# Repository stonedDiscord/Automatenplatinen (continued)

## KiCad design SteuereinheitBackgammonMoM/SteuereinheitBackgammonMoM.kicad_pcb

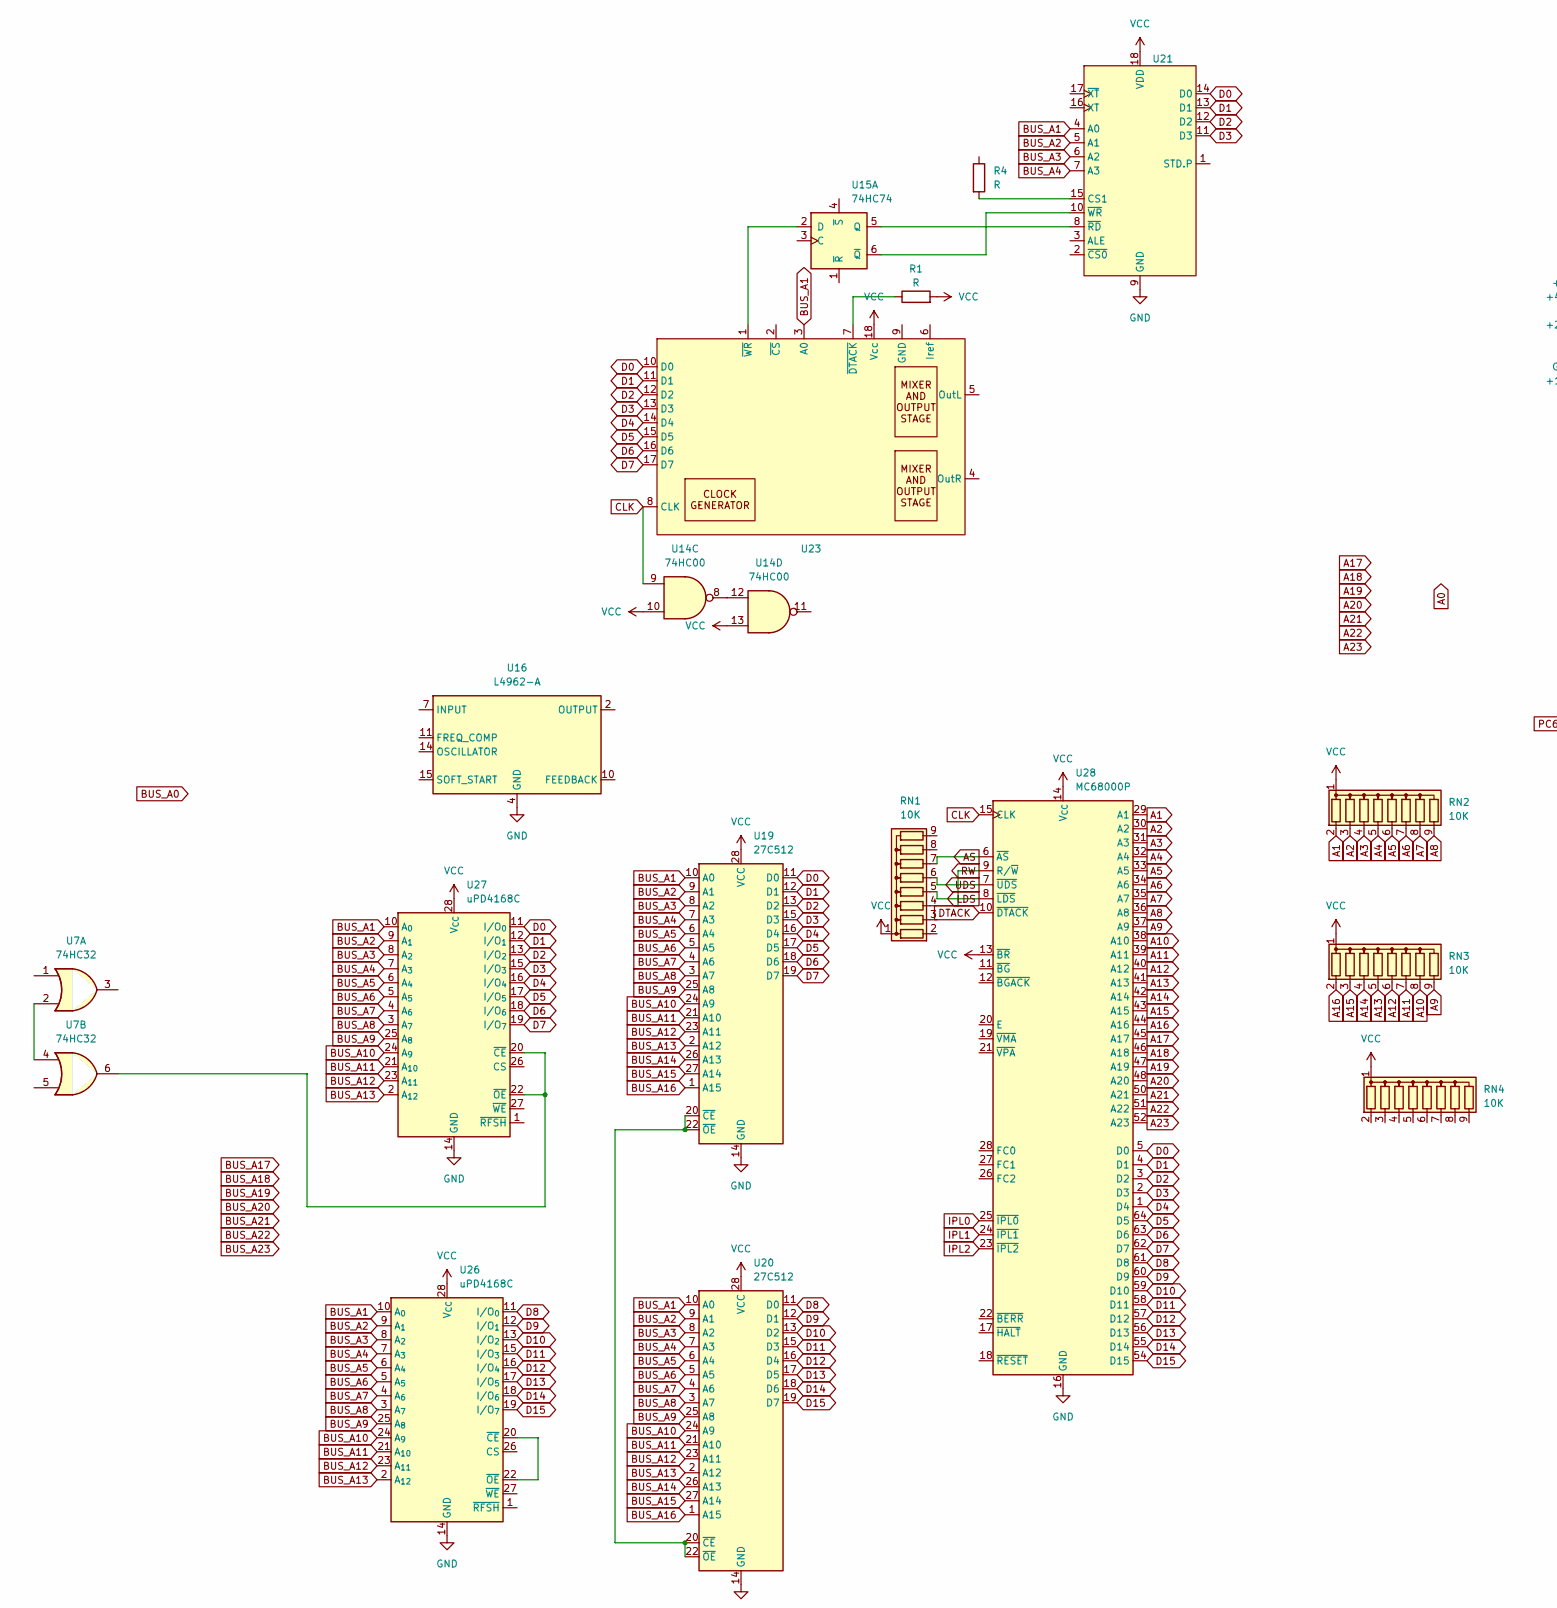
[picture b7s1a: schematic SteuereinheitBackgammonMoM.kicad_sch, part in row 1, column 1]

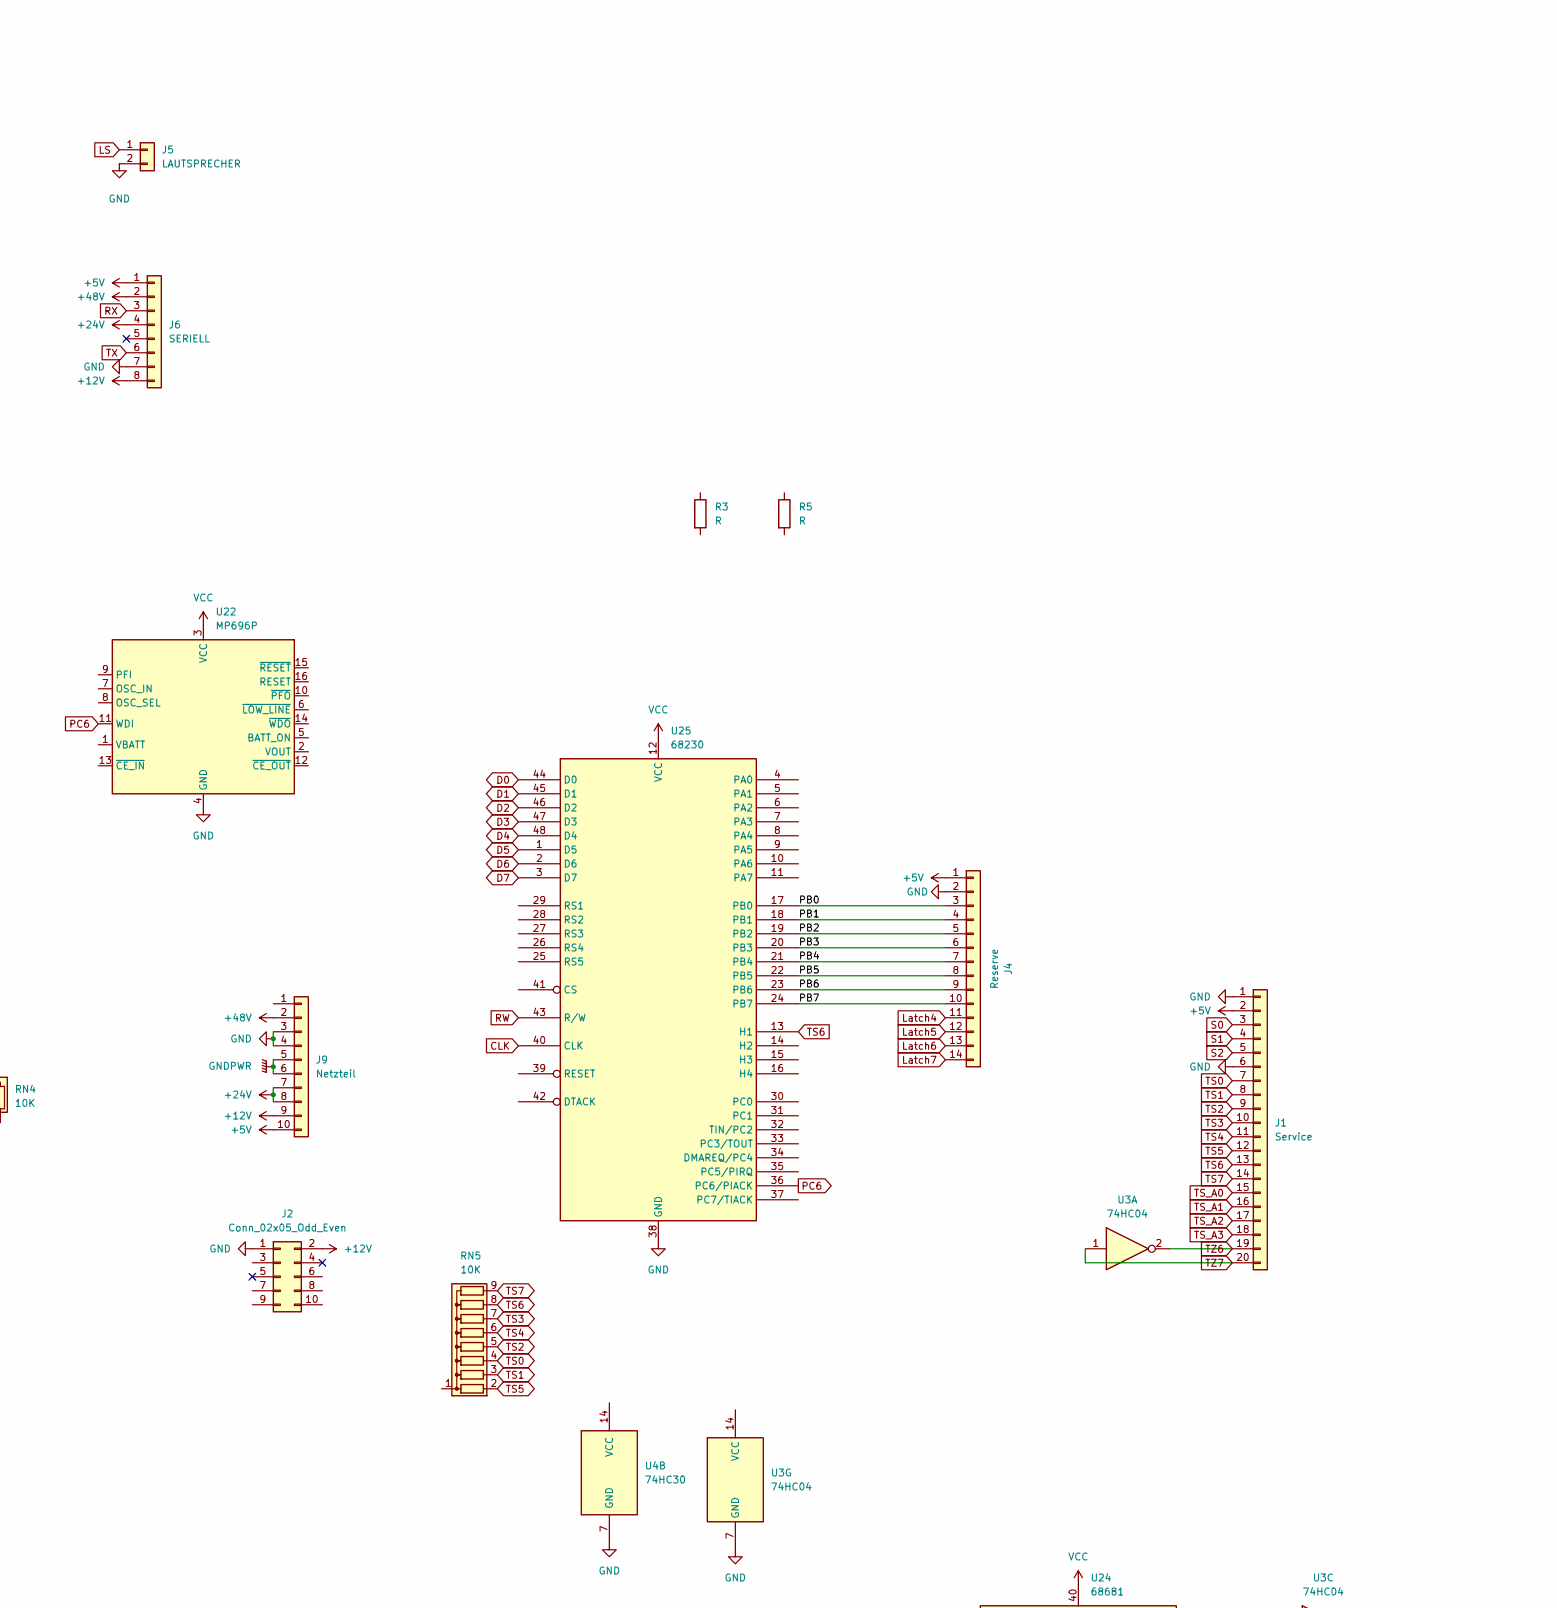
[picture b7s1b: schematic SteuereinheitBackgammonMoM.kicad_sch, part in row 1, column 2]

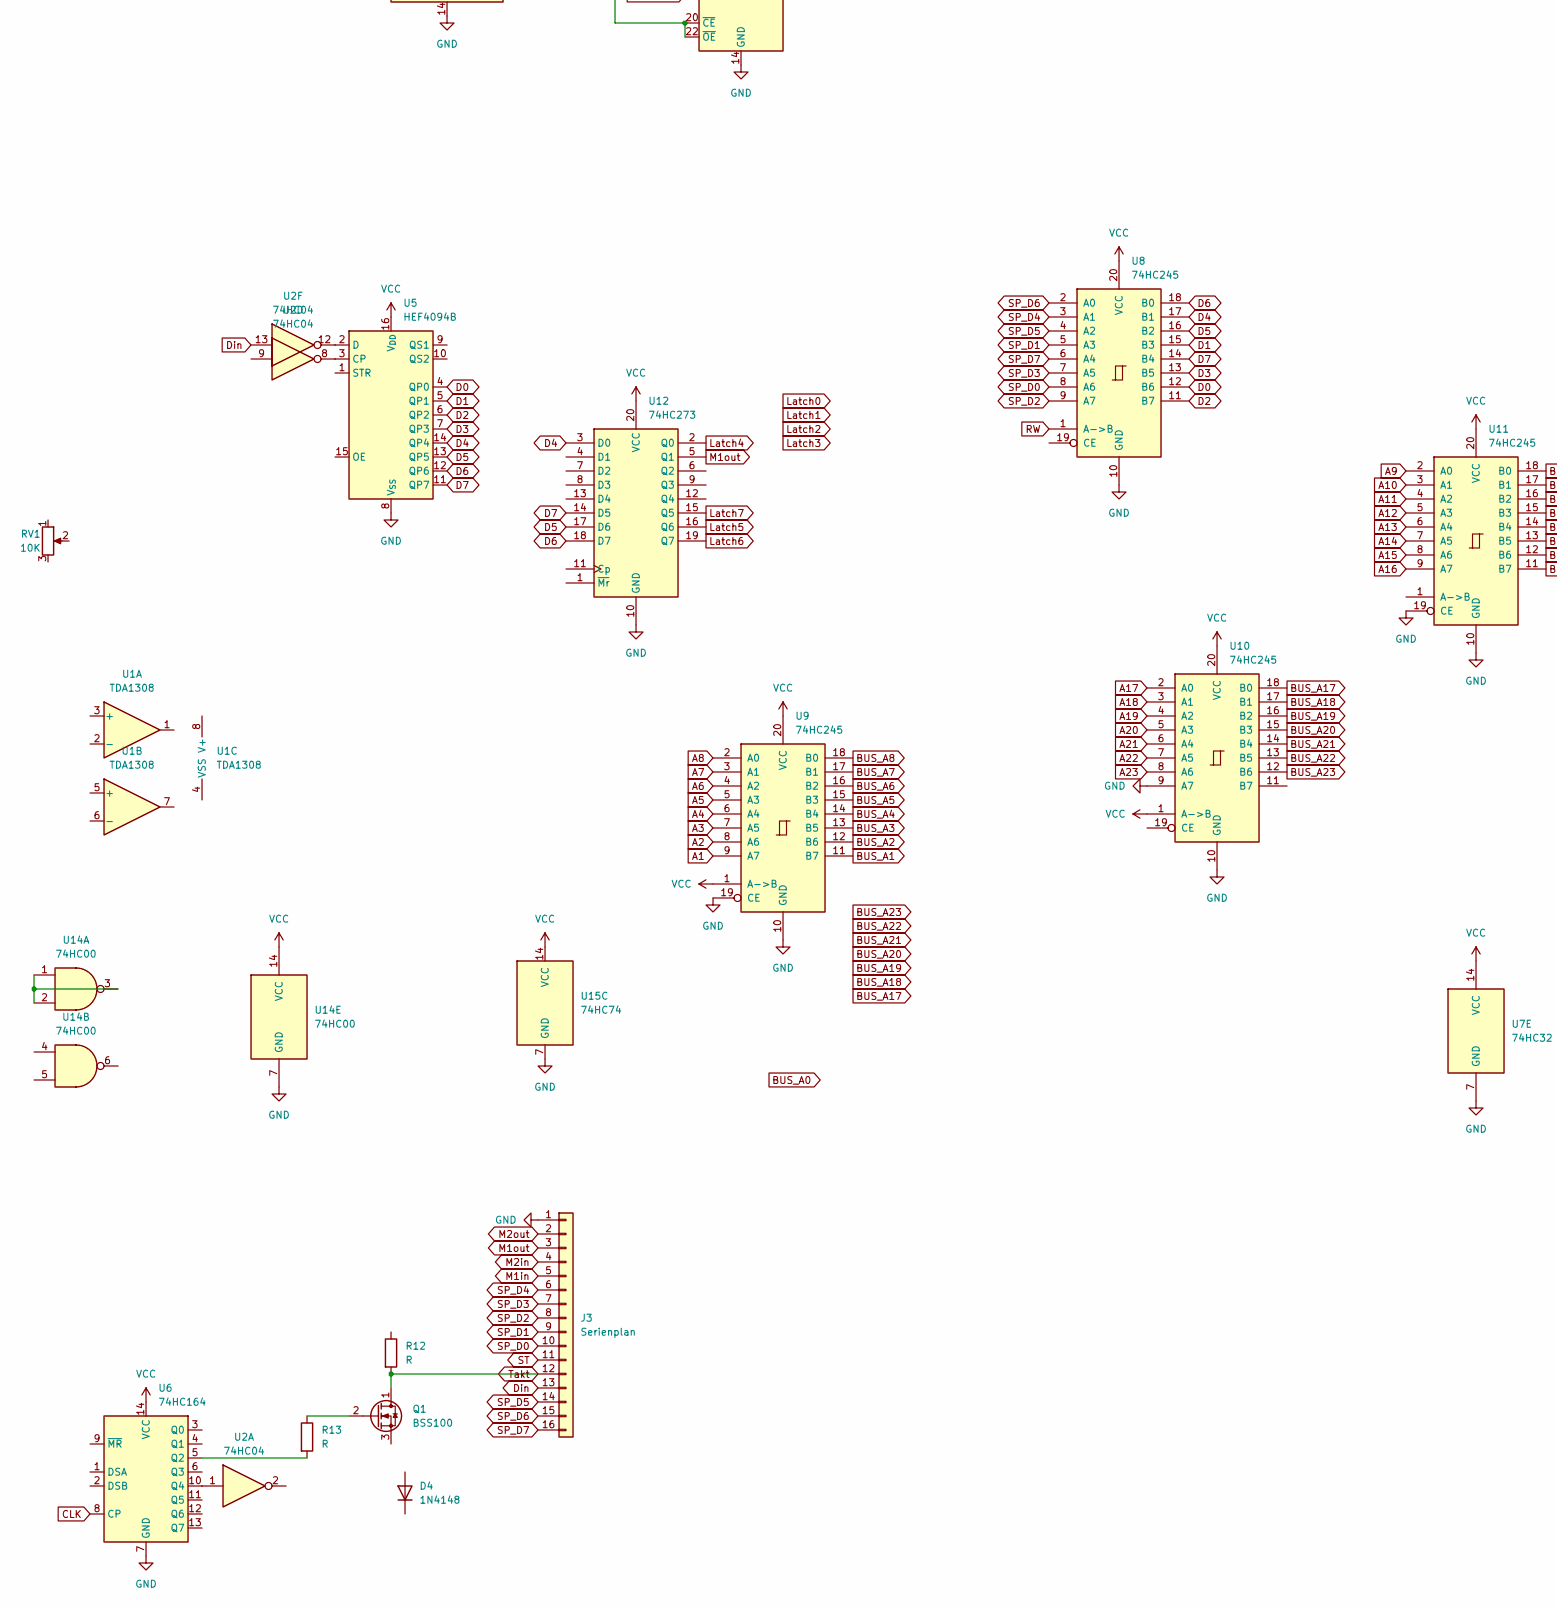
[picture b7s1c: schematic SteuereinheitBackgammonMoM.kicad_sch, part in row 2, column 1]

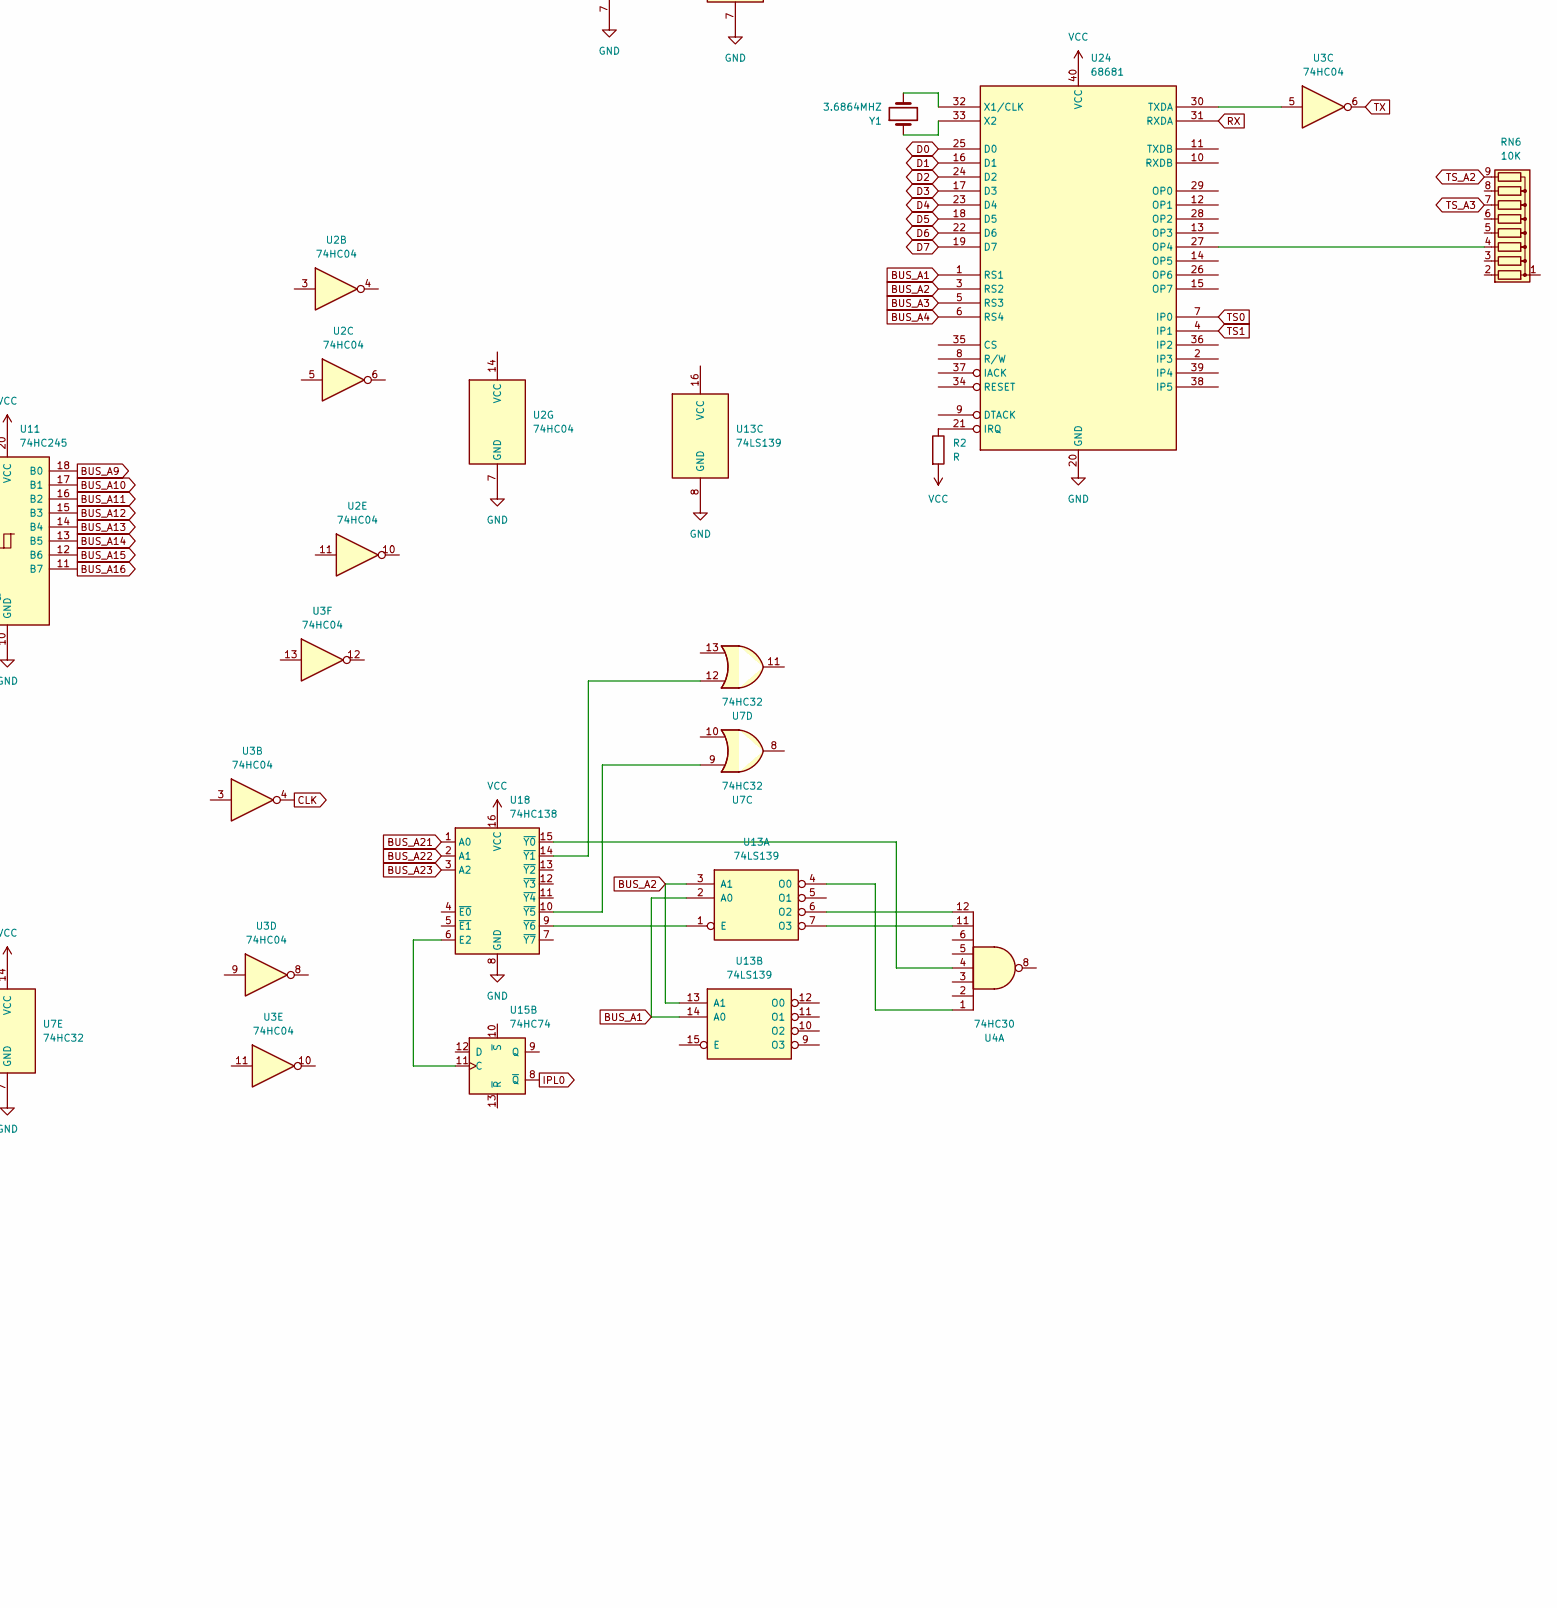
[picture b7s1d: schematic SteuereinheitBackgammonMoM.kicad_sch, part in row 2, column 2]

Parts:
D4: 1N4148; D_DO-35_SOD27_P7.62mm_Horizontal
J1: Service; Stocko_MKS_1670-6-0-2020_1x20_P2.50mm_Vertical
J2: Conn_02x05_Odd_Even; IDC-Header_2x05_P2.54mm_Vertical
J3: Serienplan; Stocko_MKS_1666-6-0-1616_1x16_P2.50mm_Vertical
J4: Reserve; Stocko_MKS_1664-6-0-1414_1x14_P2.50mm_Vertical
J5: LAUTSPRECHER; Stocko_MKS_1652-6-0-202_1x2_P2.50mm_Vertical
J6: SERIELL; Stocko_MKS_1658-6-0-808_1x8_P2.50mm_Vertical
J9: Netzteil; Stocko_MKS_1660-6-0-1010_1x10_P2.50mm_Vertical
Q1: BSS100; TO-92
R1, R2, R3, R4, R5, R12, R13: R; R_Axial_DIN0207_L6.3mm_D2.5mm_P10.16mm_Horizontal
RN1, RN2, RN3, RN4, RN5, RN6: 10K; R_Array_SIP9
RV1: 10K; Potentiometer_Piher_PT-10-V10_Vertical
U1: TDA1308
U2, U3: 74HC04; DIP-14_W7.62mm
U4: 74HC30; DIP-14_W7.62mm
U5: HEF4094B; DIP-16_W7.62mm
U6: 74HC164; DIP-14_W7.62mm
U7: 74HC32; DIP-14_W7.62mm
U8, U9, U10, U11: 74HC245; DIP-20_W7.62mm
U12: 74HC273; DIP-20_W7.62mm
U13: 74LS139; DIP-16_W7.62mm
U14: 74HC00; DIP-14_W7.62mm
U15: 74HC74; DIP-14_W7.62mm
U16: L4962-A; DIP-16_W7.62mm
U18: 74HC138; DIP-16_W7.62mm
U19, U20: 27C512; DIP-28_W15.24mm
U21, U23: DIP-18_W7.62mm
U22: MP696P; DIP-16_W7.62mm
U24: 68681; DIP-40_W15.24mm
U25: 68230; DIP-48_W15.24mm
U26, U27: uPD4168C; DIP-28_W15.24mm
U28: MC68000P; DIP-64_W22.86mm
Y1: 3.6864MHZ; Crystal_HC49-4H_Vertical

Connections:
+5V: J1.2, J4.1, J6.1, J9.10
+12V: J2.2, J6.8, J9.9
+24V: J6.4, J9.7, J9.8
+48V: J6.2, J9.2
/PB0: J4.3, U25.17 (PB0)
/PB1: J4.4, U25.18 (PB1)
/PB2: J4.5, U25.19 (PB2)
/PB3: J4.6, U25.20 (PB3)
/PB4: J4.7, U25.21 (PB4)
/PB5: J4.8, U25.22 (PB5)
/PB6: J4.9, U25.23 (PB6)
/PB7: J4.10, U25.24 (PB7)
A1: RN2.2 (R1), U9.9 (A7), U28.29 (A1)
A2: RN2.3 (R2), U9.8 (A6), U28.30 (A2)
A3: RN2.4 (R3), U9.7 (A5), U28.31 (A3)
A4: RN2.5 (R4), U9.6 (A4), U28.32 (A4)
A5: RN2.6 (R5), U9.5 (A3), U28.33 (A5)
A6: RN2.7 (R6), U9.4 (A2), U28.34 (A6)
A7: RN2.8 (R7), U9.3 (A1), U28.35 (A7)
A8: RN2.9 (R8), U9.2 (A0), U28.36 (A8)
A9: RN3.9 (R8), U11.2 (A0), U28.37 (A9)
A10: RN3.8 (R7), U11.3 (A1), U28.38 (A10)
A11: RN3.7 (R6), U11.4 (A2), U28.39 (A11)
A12: RN3.6 (R5), U11.5 (A3), U28.40 (A12)
A13: RN3.5 (R4), U11.6 (A4), U28.41 (A13)
A14: RN3.4 (R3), U11.7 (A5), U28.42 (A14)
A15: RN3.3 (R2), U11.8 (A6), U28.43 (A15)
A16: RN3.2 (R1), U11.9 (A7), U28.44 (A16)
A17: U10.2 (A0), U28.45 (A17)
A18: U10.3 (A1), U28.46 (A18)
A19: U10.4 (A2), U28.47 (A19)
A20: U10.5 (A3), U28.48 (A20)
A21: U10.6 (A4), U28.50 (A21)
A22: U10.7 (A5), U28.51 (A22)
A23: U10.8 (A6), U28.52 (A23)
AS: RN1.7 (R6), U28.6 (~AS)
BUS_A1: U9.11 (B7), U13.2 (A0), U13.14 (A0), U19.10 (A0), U20.10 (A0), U21.4 (A0), U23.3 (A0), U24.1 (RS1), U26.10 (A_{0}), U27.10 (A_{0})
BUS_A2: U9.12 (B6), U13.3 (A1), U13.13 (A1), U19.9 (A1), U20.9 (A1), U21.5 (A1), U24.3 (RS2), U26.9 (A_{1}), U27.9 (A_{1})
BUS_A3: U9.13 (B5), U19.8 (A2), U20.8 (A2), U21.6 (A2), U24.5 (RS3), U26.8 (A_{2}), U27.8 (A_{2})
BUS_A4: U9.14 (B4), U19.7 (A3), U20.7 (A3), U21.7 (A3), U24.6 (RS4), U26.7 (A_{3}), U27.7 (A_{3})
BUS_A5: U9.15 (B3), U19.6 (A4), U20.6 (A4), U26.6 (A_{4}), U27.6 (A_{4})
BUS_A6: U9.16 (B2), U19.5 (A5), U20.5 (A5), U26.5 (A_{5}), U27.5 (A_{5})
BUS_A7: U9.17 (B1), U19.4 (A6), U20.4 (A6), U26.4 (A_{6}), U27.4 (A_{6})
BUS_A8: U9.18 (B0), U19.3 (A7), U20.3 (A7), U26.3 (A_{7}), U27.3 (A_{7})
BUS_A9: U11.18 (B0), U19.25 (A8), U20.25 (A8), U26.25 (A_{8}), U27.25 (A_{8})
BUS_A10: U11.17 (B1), U19.24 (A9), U20.24 (A9), U26.24 (A_{9}), U27.24 (A_{9})
BUS_A11: U11.16 (B2), U19.21 (A10), U20.21 (A10), U26.21 (A_{10}), U27.21 (A_{10})
BUS_A12: U11.15 (B3), U19.23 (A11), U20.23 (A11), U26.23 (A_{11}), U27.23 (A_{11})
BUS_A13: U11.14 (B4), U19.2 (A12), U20.2 (A12), U26.2 (A_{12}), U27.2 (A_{12})
BUS_A14: U11.13 (B5), U19.26 (A13), U20.26 (A13)
BUS_A15: U11.12 (B6), U19.27 (A14), U20.27 (A14)
BUS_A16: U11.11 (B7), U19.1 (A15), U20.1 (A15)
BUS_A17: U10.18 (B0)
BUS_A18: U10.17 (B1)
BUS_A19: U10.16 (B2)
BUS_A20: U10.15 (B3)
BUS_A21: U10.14 (B4), U18.1 (A0)
BUS_A22: U10.13 (B5), U18.2 (A1)
BUS_A23: U10.12 (B6), U18.3 (A2)
CLK: U3.4, U6.8 (CP), U14.9, U23.8 (CLK), U25.40 (CLK), U28.15 (CLK)
D0: U5.4 (QP0), U8.12 (B6), U19.11 (D0), U21.14 (D0), U23.10 (D0), U24.25 (D0), U25.44 (D0), U27.11 (I/O_{0}), U28.5 (D0)
D1: U5.5 (QP1), U8.15 (B3), U19.12 (D1), U21.13 (D1), U23.11 (D1), U24.16 (D1), U25.45 (D1), U27.12 (I/O_{1}), U28.4 (D1)
D2: U5.6 (QP2), U8.11 (B7), U19.13 (D2), U21.12 (D2), U23.12 (D2), U24.24 (D2), U25.46 (D2), U27.13 (I/O_{2}), U28.3 (D2)
D3: U5.7 (QP3), U8.13 (B5), U19.15 (D3), U21.11 (D3), U23.13 (D3), U24.17 (D3), U25.47 (D3), U27.15 (I/O_{3}), U28.2 (D3)
D4: U5.14 (QP4), U8.17 (B1), U12.3 (D0), U19.16 (D4), U23.14 (D4), U24.23 (D4), U25.48 (D4), U27.16 (I/O_{4}), U28.1 (D4)
D5: U5.13 (QP5), U8.16 (B2), U12.17 (D6), U19.17 (D5), U23.15 (D5), U24.18 (D5), U25.1 (D5), U27.17 (I/O_{5}), U28.64 (D5)
D6: U5.12 (QP6), U8.18 (B0), U12.18 (D7), U19.18 (D6), U23.16 (D6), U24.22 (D6), U25.2 (D6), U27.18 (I/O_{6}), U28.63 (D6)
D7: U5.11 (QP7), U8.14 (B4), U12.14 (D5), U19.19 (D7), U23.17 (D7), U24.19 (D7), U25.3 (D7), U27.19 (I/O_{7}), U28.62 (D7)
D8: U20.11 (D0), U26.11 (I/O_{0}), U28.61 (D8)
D9: U20.12 (D1), U26.12 (I/O_{1}), U28.60 (D9)
D10: U20.13 (D2), U26.13 (I/O_{2}), U28.59 (D10)
D11: U20.15 (D3), U26.15 (I/O_{3}), U28.58 (D11)
D12: U20.16 (D4), U26.16 (I/O_{4}), U28.57 (D12)
D13: U20.17 (D5), U26.17 (I/O_{5}), U28.56 (D13)
D14: U20.18 (D6), U26.18 (I/O_{6}), U28.55 (D14)
D15: U20.19 (D7), U26.19 (I/O_{7}), U28.54 (D15)
DTACK: U28.10 (~DTACK)
Din: J3.13, U2.13
GND: J1.1, J1.6, J2.1, J3.1, J4.2, J5.2, J6.7, J9.3, J9.4, U2.7 (GND_7), U3.7 (GND_7), U4.7 (GND_7), U5.8 (V_{SS}), U6.7 (GND), U7.7 (GND), U8.10 (GND), U9.10 (GND), U9.19 (CE), U10.9 (A7), U10.10 (GND), U11.10 (GND), U11.19 (CE), U12.10 (GND), U13.8 (GND), U14.7 (GND), U15.7 (GND), U16.4 (GND), U16.5 (GND), U16.12 (GND), U16.13 (GND), U18.8 (GND), U19.14 (GND), U20.14 (GND), U21.9 (GND), U22.4 (GND), U24.20 (GND), U25.38 (GND), U26.14 (GND), U27.14 (GND), U28.16 (GND), U28.53 (GND)
GNDPWR: J9.5, J9.6
IPL0: U15.8 (~Q), U28.25 (~IPL0)
IPL1: U28.24 (~IPL1)
IPL2: U28.23 (~IPL2)
LDS: RN1.5 (R4), U28.8 (~LDS)
LS: J5.1
Latch4: J4.11, U12.2 (Q0)
Latch5: J4.12, U12.16 (Q6)
Latch6: J4.13, U12.19 (Q7)
Latch7: J4.14, U12.15 (Q5)
M1in: J3.5
M1out: J3.3, U12.5 (Q1)
M2in: J3.4
M2out: J3.2
unnamed: Q1.2 (G), R13.1
unnamed: RN6.4 (R3), U24.27 (OP4)
unnamed: U2.8, U5.3 (CP)
unnamed: U2.12, U5.2 (D)
unnamed: R13.2, U6.5 (Q2)
unnamed: U2.1, U6.10 (Q4)
unnamed: U7.2, U7.4
unnamed: U13.1 (E), U18.9 (~Y6)
unnamed: U4.1, U13.4 (O0)
unnamed: U4.12, U13.6 (O2)
unnamed: U4.11, U13.7 (O3)
unnamed: U14.1, U14.2, U14.3
unnamed: U14.8, U14.12
unnamed: U15.2 (D), U23.1 (~WR)
unnamed: U15.5 (Q), U21.8 (~RD)
unnamed: U15.6 (~Q), U21.10 (~WR)
unnamed: U15.11 (C), U18.6 (E2)
unnamed: U4.4, U18.15 (~Y0)
unnamed: U7.12, U18.14 (~Y1)
unnamed: U7.9, U18.10 (~Y5)
unnamed: U19.20 (~CE), U19.22 (~OE), U20.20 (~CE), U20.22 (~OE)
unnamed: R4.2, U21.15 (CS1)
unnamed: R1.1, U23.7 (~DTACK)
unnamed: R2.1, U24.21 (IRQ)
unnamed: U3.5, U24.30 (TXDA)
unnamed: U24.32 (X1/CLK), Y1.2
unnamed: U24.33 (X2), Y1.1
unnamed: U26.20 (~CE), U26.22 (~OE)
unnamed: U7.6, U27.20 (~CE), U27.22 (~OE)
PC6: U22.11 (WDI), U25.36 (PC6/PIACK)
RW: RN1.4 (R3), U8.1 (A->B), U25.43 (R/W), U28.9 (R/~W)
RX: J6.3, U24.31 (RXDA)
S0: J1.3
S1: J1.4
S2: J1.5
SP_D0: J3.10, U8.8 (A6)
SP_D1: J3.9, U8.5 (A3)
SP_D2: J3.8, U8.9 (A7)
SP_D3: J3.7, U8.7 (A5)
SP_D4: J3.6, U8.3 (A1)
SP_D5: J3.14, U8.4 (A2)
SP_D6: J3.15, U8.2 (A0)
SP_D7: J3.16, U8.6 (A4)
ST: J3.11
TS0: J1.7, RN5.4 (R3), U24.7 (IP0)
TS1: J1.8, RN5.3 (R2), U24.4 (IP1)
TS2: J1.9, RN5.5 (R4)
TS3: J1.10, RN5.7 (R6)
TS4: J1.11, RN5.6 (R5)
TS5: J1.12, RN5.2 (R1)
TS6: J1.13, RN5.8 (R7), U25.13 (H1)
TS7: J1.14, RN5.9 (R8)
TS_A0: J1.15
TS_A1: J1.16
TS_A2: J1.17, RN6.9 (R8)
TS_A3: J1.18, RN6.7 (R6)
TX: J6.6, U3.6
TZ6: J1.19, U3.2
TZ7: J1.20, U3.1
Takt: J3.12, Q1.1 (D), R12.2
UDS: RN1.6 (R5), U28.7 (~UDS)
VCC: R1.2, R2.2, RN1.1 (common), RN2.1 (common), RN3.1 (common), RN4.1 (common_1), U5.16 (V_{DD}), U6.14 (VCC), U7.14 (VCC), U8.20 (VCC), U9.1 (A->B), U9.20 (VCC), U10.1 (A->B), U10.20 (VCC), U11.20 (VCC), U12.20 (VCC), U14.10, U14.13, U14.14 (VCC), U15.14 (VCC), U18.16 (VCC), U19.28 (VCC), U20.28 (VCC), U21.18 (VDD), U22.3 (VCC), U23.18 (Vcc), U24.40 (VCC), U25.12 (VCC), U26.28 (V_{CC}), U27.28 (V_{CC}), U28.13 (~BR), U28.14 (V_{CC}), U28.49 (V_{CC})

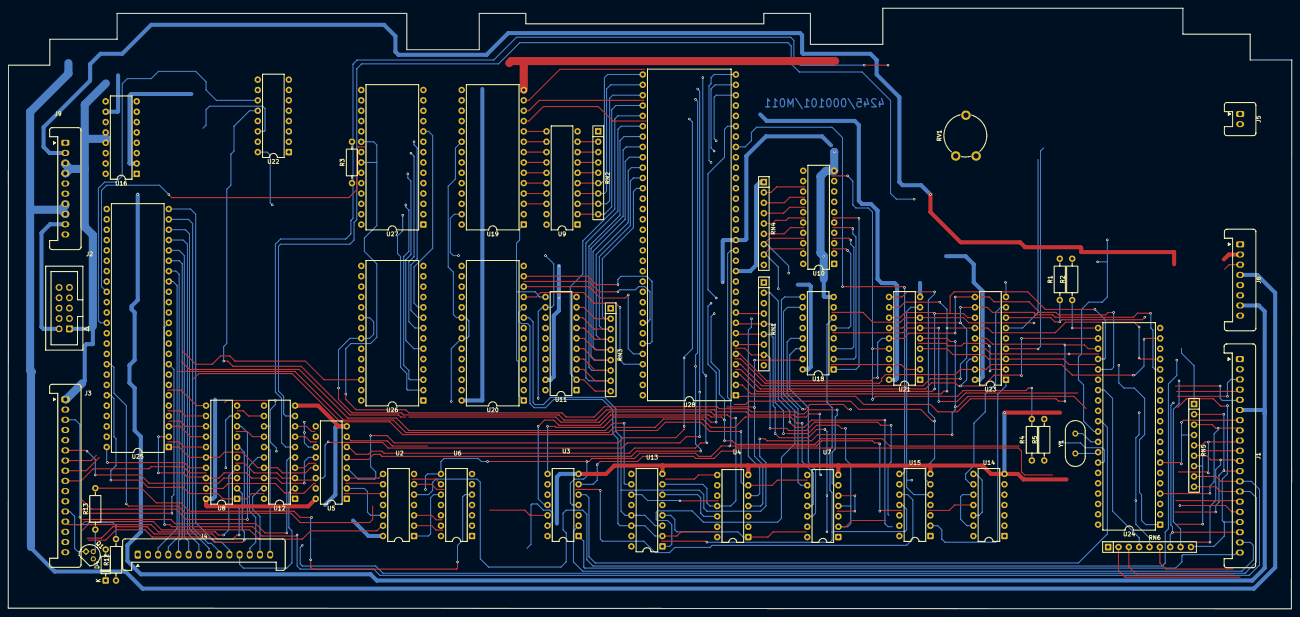
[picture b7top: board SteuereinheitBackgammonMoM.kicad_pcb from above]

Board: 2 copper layers, 315.0 x 147.4 mm, 50 parts (0 on the bottom side), 138 nets.
